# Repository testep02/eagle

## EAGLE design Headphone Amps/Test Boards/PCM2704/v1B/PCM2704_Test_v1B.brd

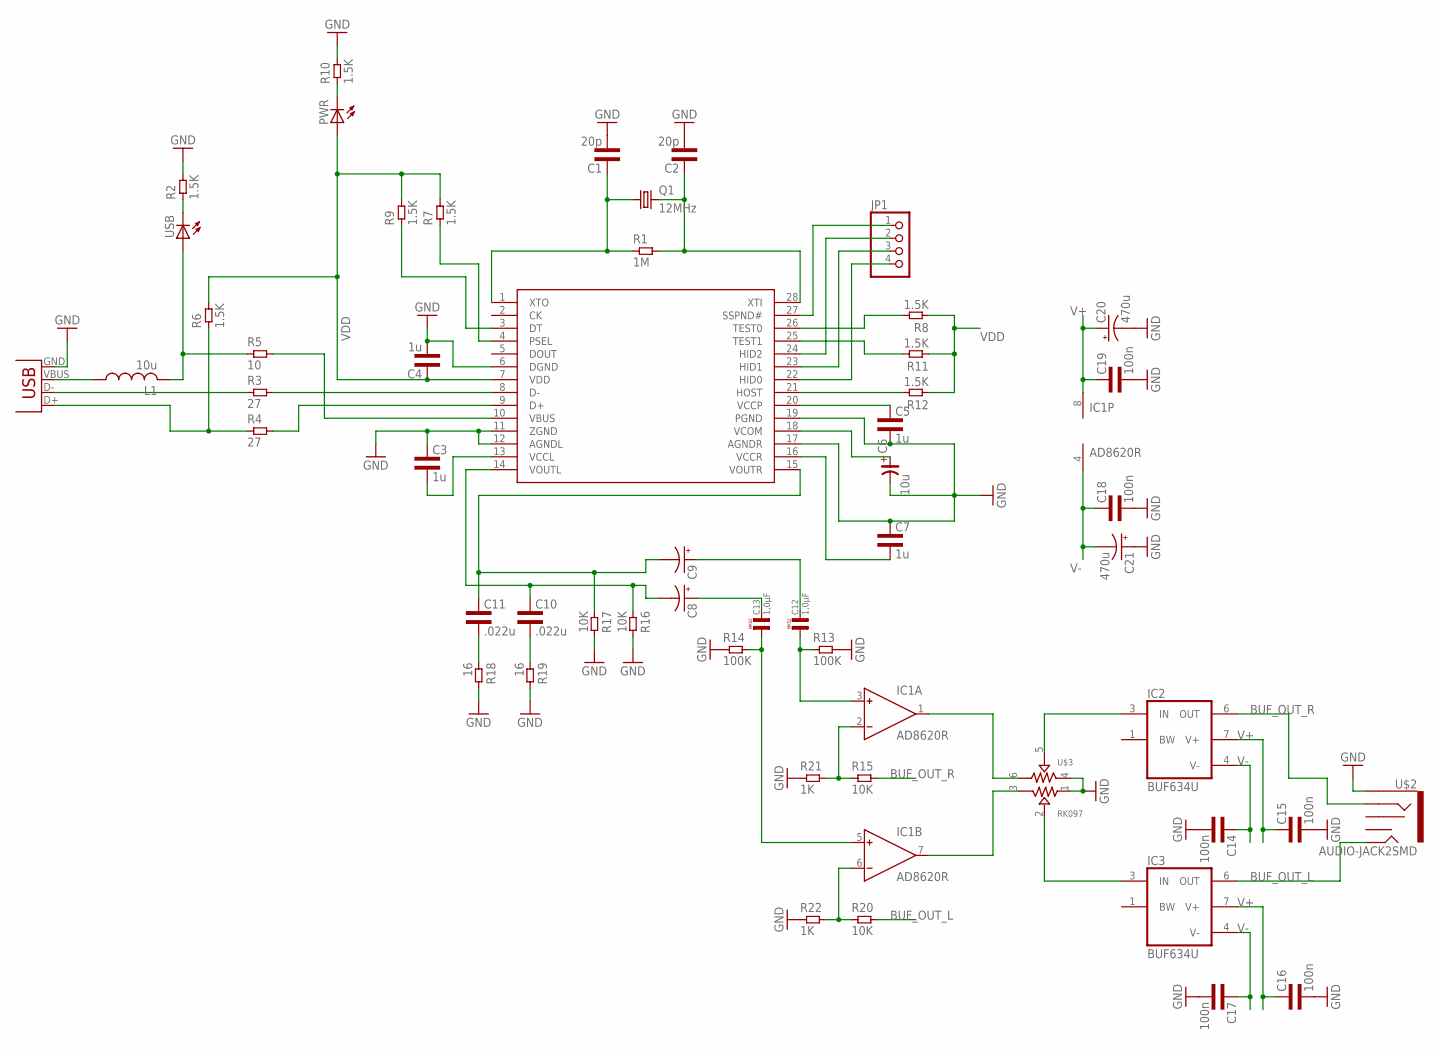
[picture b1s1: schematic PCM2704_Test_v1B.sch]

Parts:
C1, C2: 20p; 0603L3
C3, C4, C5, C7: 1u; 0603L3
C6: 10u; CE-010X030
C8, C9: CPOL-USE1.8-4; E1,8-4
C10, C11: .022u; 0603L3
C12, C13: 1,0µF; R5B5
C14, C15, C16, C17, C18, C19: 100n; 0603L3
C20, C21: 470u; E5-13
IC1: AD8620R; SO8
IC2, IC3: BUF634U; SO08
JP1: PINHD-1X4; 1X04
L1: 10u; L3225M
PWR: LEDCHIP-LED0603; CHIP-LED0603
Q1: 12MHz; HC49US
R1: 1M; 0603L3
R2, R6, R7, R8, R9, R10, R11, R12: 1.5K; 0603L3
R3, R4: 27; 0603L3
R5: 10; 0805L3
R13, R14: 100K; 0603L3
R15, R16, R17, R20: 10K; 0603L3
R18, R19: 16; 0603L3
R21, R22: 1K; 0603L3
U$1: PCM2704C
U$2: AUDIO-JACK2SMD; AUDIO-JACK-3.5MM-SMD
U$3: RK097
USB: LEDCHIP-LED0603; CHIP-LED0603
X1: USB-MB-S

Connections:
BUF_OUT_L: IC3.6 (OUT), R20.P$2 (2), U$2.TIP
BUF_OUT_R: IC2.6 (OUT), R15.P$2 (2), U$2.RING
GND: C1.P$2 (2), C2.P$2 (2), C3.P$1 (1), C4.P$2 (2), C5.P$2 (2), C6.-, C7.P$1 (1), C14.P$2 (2), C15.P$2 (2), C16.P$2 (2), C17.P$2 (2), C18.P$2 (2), C19.P$2 (2), C20.-, C21.+, R2.P$2 (2), R10.P$2 (2), R13.P$2 (2), R14.P$1 (1), R16.P$2 (2), R17.P$2 (2), R18.P$2 (2), R19.P$2 (2), R21.P$1 (1), R22.P$1 (1), U$1.6 (DGND), U$1.11 (ZGND), U$1.12 (AGNDL), U$1.17 (AGNDR), U$1.19 (PGND), U$2.SLEEVE, U$3.1, U$3.4, X1.GND
unnamed: C1.P$1 (1), Q1.1, R1.P$1 (1), U$1.1 (XTO)
unnamed: C2.P$1 (1), Q1.2, R1.P$2 (2), U$1.28 (XTI)
unnamed: R3.P$2 (2), U$1.8 (D-)
unnamed: C3.P$2 (2), U$1.13 (VCCL)
unnamed: R8.P$2 (2), U$1.26 (TEST0)
unnamed: R4.P$2 (2), U$1.9 (D+)
unnamed: L1.2, R5.1, USB.A
unnamed: R5.2, U$1.10 (VBUS)
unnamed: R11.P$2 (2), U$1.25 (TEST1)
unnamed: C9.-, C11.P$1 (1), R17.P$1 (1), U$1.15 (VOUTR)
unnamed: R12.P$2 (2), U$1.21 (HOST)
unnamed: JP1.1, U$1.27 (SSPND#)
unnamed: C5.P$1 (1), U$1.20 (VCCP)
unnamed: C6.+, U$1.18 (VCOM)
unnamed: C8.+, C13.2
unnamed: R9.P$1 (1), U$1.3 (DT)
unnamed: R2.P$1 (1), USB.C
unnamed: C9.+, C12.2
unnamed: JP1.2, U$1.24 (HID2)
unnamed: JP1.3, U$1.23 (HID1)
unnamed: JP1.4, U$1.22 (HID0)
unnamed: PWR.C, R10.P$1 (1)
unnamed: C7.P$2 (2), U$1.16 (VCCR)
unnamed: C8.-, C10.P$1 (1), R16.P$1 (1), U$1.14 (VOUTL)
unnamed: C12.1, IC1.3 (IN+), R13.P$1 (1)
unnamed: C13.1, IC1.5 (IN+), R14.P$2 (2)
unnamed: C11.P$2 (2), R18.P$1 (1)
unnamed: C10.P$2 (2), R19.P$1 (1)
unnamed: IC1.2 (IN-), R15.P$1 (1), R21.P$2 (2)
unnamed: IC1.6 (IN-), R20.P$1 (1), R22.P$2 (2)
unnamed: IC2.3 (IN), U$3.5
unnamed: IC3.3 (IN), U$3.2
unnamed: IC1.1 (OUT), U$3.6
unnamed: IC1.7 (OUT), U$3.3
PSEL: R7.P$1 (1), U$1.4 (PSEL)
USB_D_N: R3.P$1 (1), X1.D-
USB_D_P: R4.P$1 (1), R6.P$1 (1), X1.D+
V+: C15.P$1 (1), C16.P$1 (1), C19.P$1 (1), C20.+, IC1.8 (V+), IC2.7 (V+), IC3.7 (V+)
V-: C14.P$1 (1), C17.P$1 (1), C18.P$1 (1), C21.-, IC1.4 (V-), IC2.4 (V-), IC3.4 (V-)
VBUS_RAW: L1.1, X1.VBUS
VDD: C4.P$1 (1), PWR.A, R6.P$2 (2), R7.P$2 (2), R8.P$1 (1), R9.P$2 (2), R11.P$1 (1), R12.P$1 (1), U$1.7 (VDD)

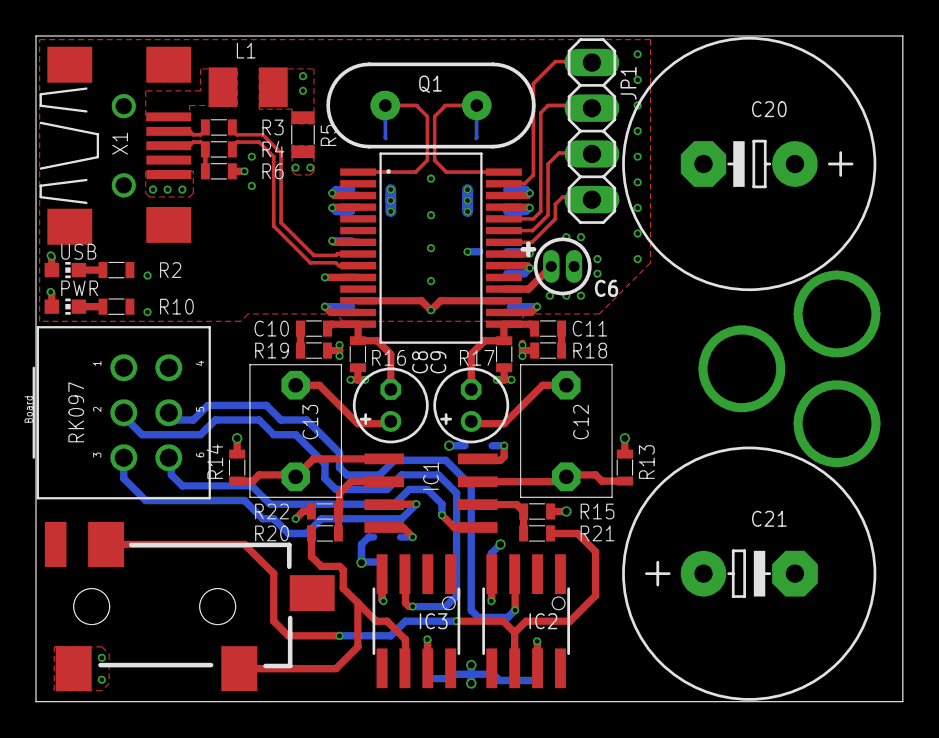
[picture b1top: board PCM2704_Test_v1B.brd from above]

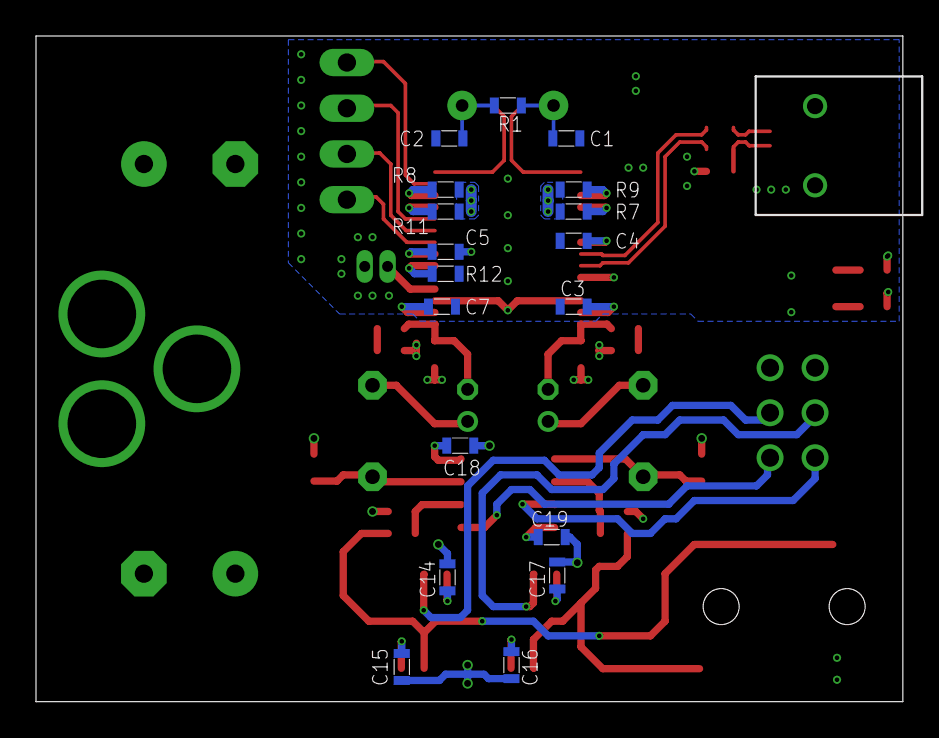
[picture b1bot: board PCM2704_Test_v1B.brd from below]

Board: 4 copper layers, 48.2 x 37.0 mm, 55 parts (18 on the bottom side), 44 nets.

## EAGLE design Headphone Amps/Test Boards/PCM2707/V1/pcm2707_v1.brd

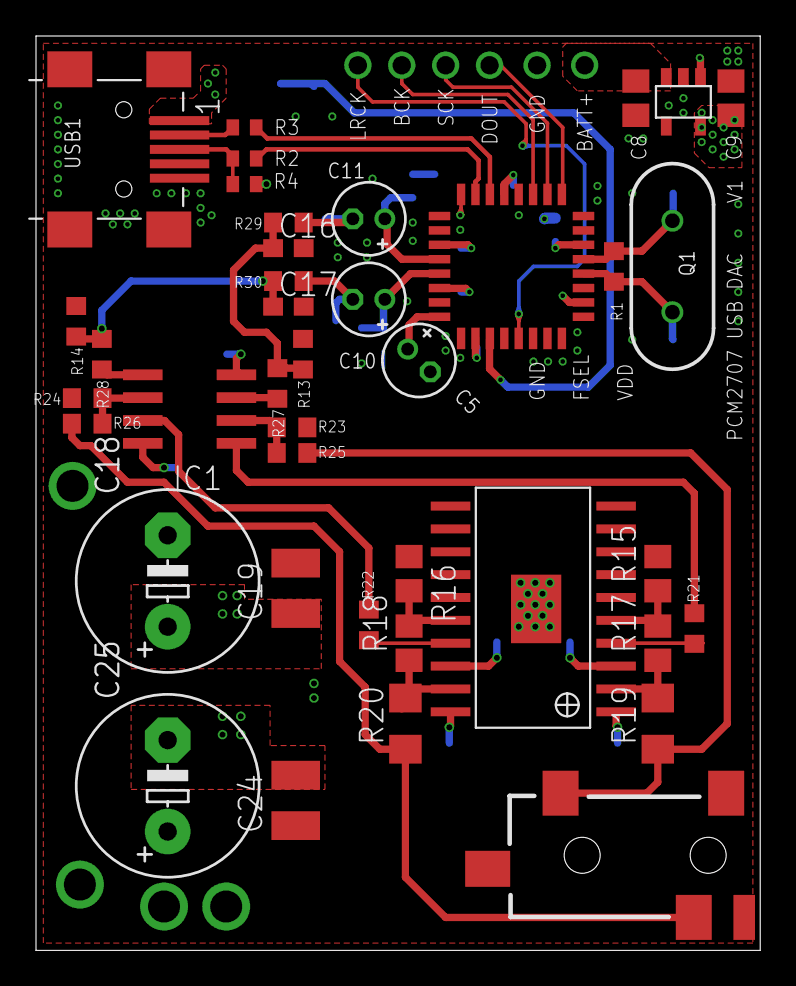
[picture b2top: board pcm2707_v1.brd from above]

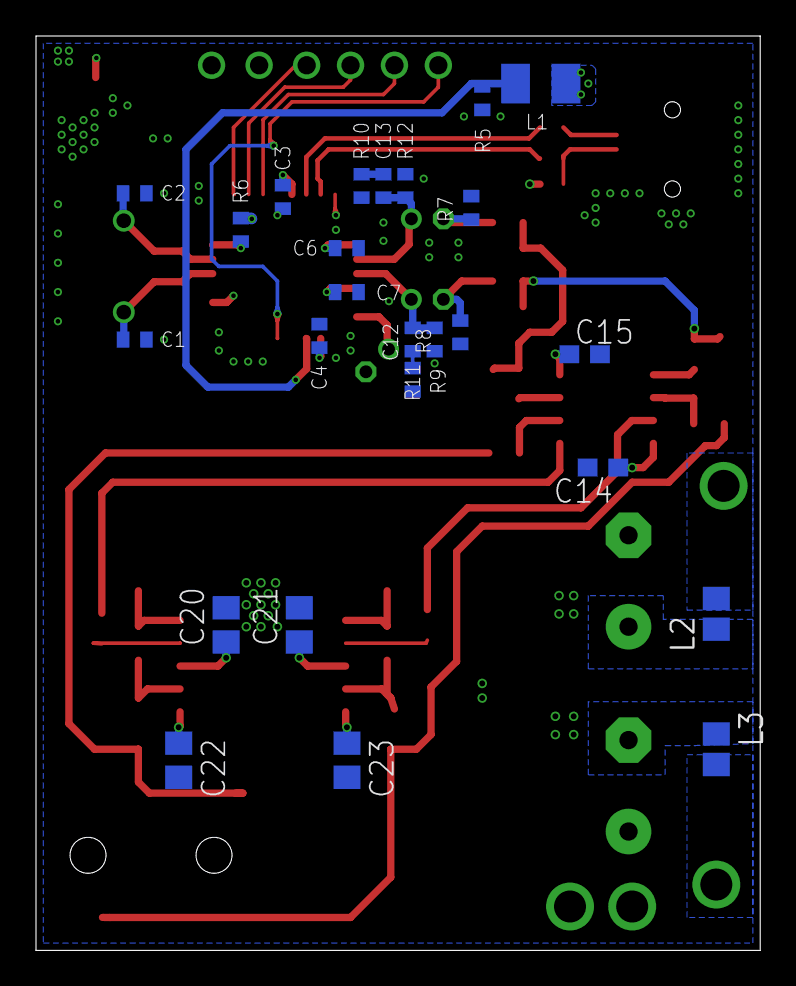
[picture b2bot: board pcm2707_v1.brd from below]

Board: 4 copper layers, 40.2 x 50.8 mm, 65 parts (25 on the bottom side), 37 nets.

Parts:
C1, C2: C0402
C3, C4, C6, C7, C12, C13: 100n; C0402
C5: E1,8-4
C8, C9: 1u; C0805
C10, C11: 100u; E1,8-4
C14: C0603
C15: 100n; C0603
C16, C17: 100p; C0603
C18, C25: 100u; E5-10,5
C19, C24: 10u; C1210
C20, C21, C22, C23: 100n; C0805
IC1: AD8620R; SO8
J2: AUDIO-JACK2SMD; AUDIO-JACK-3.5MM-SMD
L1: L3225M
L2, L3: FB805
LDO1: 3.3V; SOT-23
Q1: HC49US
R1: 1M; R0603
R2, R3, R4, R7, R8, R9, R10, R11, R12: 22; R0402
R5, R6: 1M; R0402
R13, R14: 22K; R0603
R15, R16, R17, R18: 1K; R0805
R19, R20: 10; R1206
R21, R22, R27, R28: 100; R0603
R23, R24, R29, R30: 1K; R0603
R25, R26: 2K; R0603
U$1: PCM2707
U$2: TPA6120_TPA6120
USB1: CON-USB-F-MINI-B; CONN_USB_MINI-B

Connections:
AMP_OUT_L: J2.TIP, R19.1, R25.2
AMP_OUT_R: J2.RING, R20.1, R26.1
D+: R2.1, U$1.23
D-: R3.1, U$1.22
DAC_OUT_L: C11.-, R7.2, R29.1
DAC_OUT_R: C10.-, R8.2, R30.1
GND: C1.1, C2.1, C3.2, C4.2, C5.-, C6.2, C7.2, C8.2, C9.2, C16.2, C17.2, C18.-, C19.2, C20.2, C21.2, C22.2, C23.2, C24.1, C25.+, J2.SLEEVE, LDO1.2, R5.2, R7.1, R8.1, R9.1, R10.1, R11.1, R12.1, R13.1, R14.1, R15.2, R16.1, R23.2, R24.2, U$1.1, U$1.16, U$1.20, U$1.25, U$1.26, U$1.31, U$2.6, U$2.7, U$2.8, U$2.9, U$2.10, U$2.11, U$2.12, U$2.13, U$2.14, U$2.15, U$2.21
unnamed: C5.+, U$1.32
unnamed: C10.+, C12.1, R11.2, U$1.29
unnamed: C11.+, C13.1, R12.2, U$1.28
unnamed: IC1.5, R28.2
unnamed: IC1.3, R27.2
unnamed: C12.2, R9.2
unnamed: C13.2, R10.2
unnamed: R6.1, U$1.14
unnamed: IC1.1, R21.2
unnamed: C16.1, R13.2, R27.1, R29.2
unnamed: IC1.7, R22.2
unnamed: C17.1, R14.2, R28.1, R30.2
unnamed: IC1.2, R23.1, R25.1
unnamed: IC1.6, R24.1, R26.2
unnamed: R17.1, R19.2, U$2.2
unnamed: R18.1, R20.2, U$2.19
unnamed: R15.1, R17.2, U$2.5
unnamed: R16.2, R18.2, U$2.16
unnamed: R21.1, U$2.4
unnamed: R22.1, U$2.17
USB_DN: R3.2, USB1.D-
USB_DP: R2.2, R4.1, USB1.D+
USB_VBUS: L1.1, USB1.VUSB
V+: C14.1, C18.+, C19.1, C20.1, C21.1, IC1.8, L2.1, U$2.3, U$2.18
V-: C15.1, C22.1, C23.1, C24.2, C25.-, IC1.4, L3.1, U$2.1, U$2.20
VBUS: L1.2, R5.1, U$1.3
VDD: C3.1, C4.1, C6.1, C7.1, C9.1, LDO1.5, R4.2, R6.2, U$1.2, U$1.10, U$1.21, U$1.24, U$1.27, U$1.30
VIN: C8.1, LDO1.1, LDO1.3
XTI: C1.2, Q1.1, R1.1, U$1.12
XTO: C2.2, Q1.2, R1.2, U$1.13

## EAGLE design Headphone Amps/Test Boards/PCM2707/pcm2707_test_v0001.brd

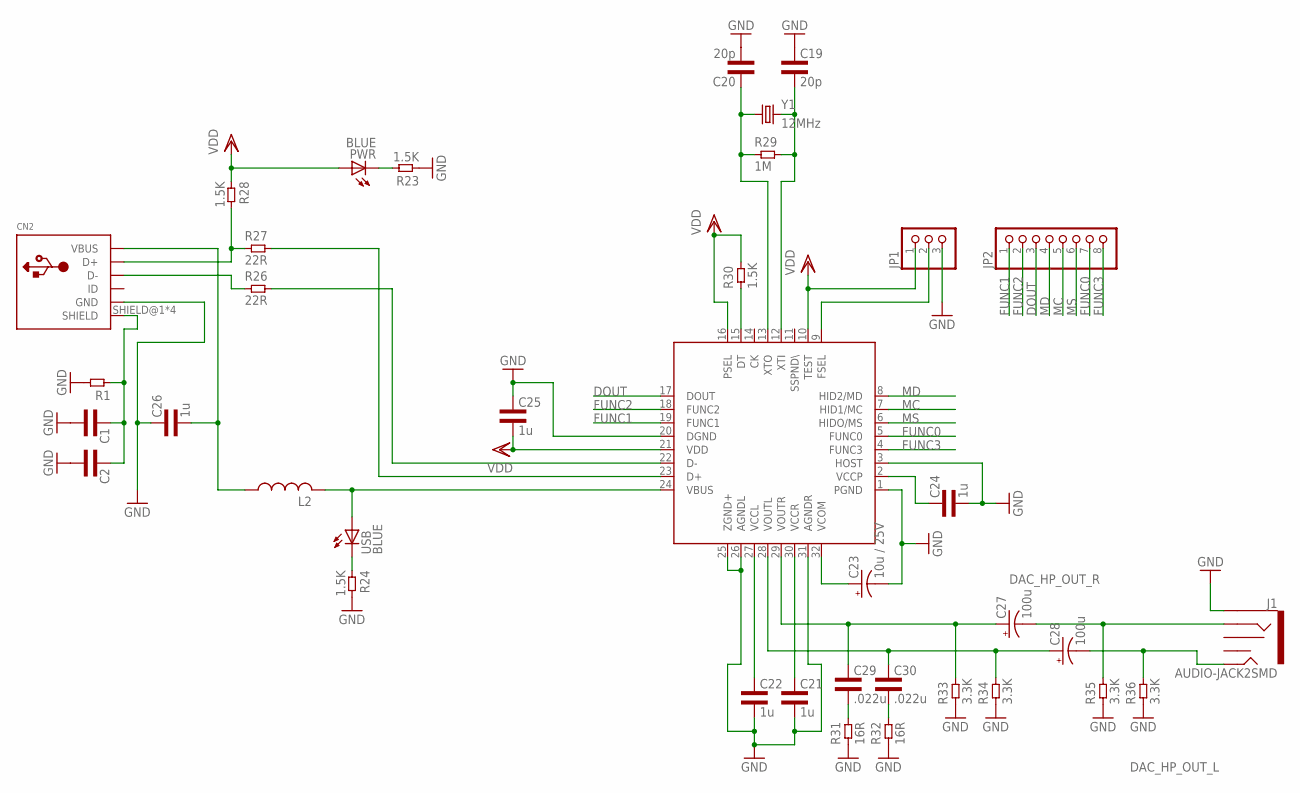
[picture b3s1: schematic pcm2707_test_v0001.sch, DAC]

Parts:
C1, C2: CAP0603L3; 0603L3
C19, C20: 20p; 0603L3
C21, C22, C24, C25, C26: 1u; 0603L3
C23: 10u / 25V; E1,8-4
C27, C28: 100u; E2-5
C29, C30: .022u; 0603L3
CN2: USBMINIB; USB-MINIB
J1: AUDIO-JACK2SMD; AUDIO-JACK-3.5MM-SMD
JP1: PINHD-1X3; 1X03
JP2: PINHD-1X8; 1X08
L2: RCL_L-USL3225M; RCL_L3225M
PWR: BLUE; LED-0603
R1: RES0603L3; 0603L3
R23, R24, R28, R30: 1.5K; 0603L3
R26, R27: 22R; 0603L3
R29: 1M; 0603L3
R31, R32: 16R; 0603L3
R33, R34, R35, R36: 3.3K; 0603L3
U$1: PCM2707_V1_PCM2704C_PCM2707
USB: BLUE; LED-0603
Y1: 12MHz; HC49US

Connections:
DAC_HP_OUT_L: C28.-, J1.TIP, R36.P$2 (2)
DAC_HP_OUT_R: C27.-, J1.RING, R35.P$2 (2)
DOUT: JP2.3, U$1.17 (DOUT)
FUNC0: JP2.7, U$1.5 (FUNC0)
FUNC1: JP2.1, U$1.19 (FUNC1)
FUNC2: JP2.2, U$1.18 (FUNC2)
FUNC3: JP2.8, U$1.4 (FUNC3)
GND: C1.P$2 (2), C2.P$2 (2), C19.P$1 (1), C20.P$2 (2), C21.P$2 (2), C22.P$2 (2), C23.-, C24.P$2 (2), C25.P$1 (1), C26.P$1 (1), CN2.GND, J1.SLEEVE, JP1.3, R1.P$2 (2), R23.P$1 (1), R24.P$2 (2), R31.P$1 (1), R32.P$1 (1), R33.P$1 (1), R34.P$1 (1), R35.P$1 (1), R36.P$1 (1), U$1.1 (PGND), U$1.3 (HOST), U$1.20 (DGND), U$1.25 (ZGND+), U$1.26 (AGNDL), U$1.31 (AGNDR)
MC: JP2.5, U$1.7 (HID1/MC)
MD: JP2.4, U$1.8 (HID2/MD)
MS: JP2.6, U$1.6 (HIDO/MS)
unnamed: JP1.2, U$1.9 (FSEL)
unnamed: PWR.C, R23.P$2 (2)
unnamed: C1.P$1 (1), C2.P$1 (1), CN2.SHIELD@1 (SHIELD), CN2.SHIELD@2 (SHIELD), CN2.SHIELD@3 (SHIELD), CN2.SHIELD@4 (SHIELD), R1.P$1 (1)
unnamed: R24.P$1 (1), USB.C
unnamed: CN2.D+, R27.P$1 (1), R28.P$2 (2)
unnamed: CN2.D-, R26.P$1 (1)
unnamed: R27.P$2 (2), U$1.23 (D+)
unnamed: R26.P$2 (2), U$1.22 (D-)
unnamed: C20.P$1 (1), R29.P$1 (1), U$1.13 (XTO), Y1.1
unnamed: C19.P$2 (2), R29.P$2 (2), U$1.12 (XTI), Y1.2
unnamed: C22.P$1 (1), U$1.27 (VCCL)
unnamed: C21.P$1 (1), U$1.30 (VCCR)
unnamed: C23.+, U$1.32 (VCOM)
unnamed: C29.P$2 (2), R31.P$2 (2)
unnamed: C24.P$1 (1), U$1.2 (VCCP)
unnamed: C27.+, C29.P$1 (1), R33.P$2 (2), U$1.29 (VOUTR)
unnamed: C28.+, C30.P$1 (1), R34.P$2 (2), U$1.28 (VOUTL)
unnamed: R30.P$1 (1), U$1.15 (DT)
unnamed: C30.P$2 (2), R32.P$2 (2)
VBUS: L2.2, U$1.24 (VBUS), USB.A
VBUS_RAW: C26.P$2 (2), CN2.VBUS, L2.1
VDD: C25.P$2 (2), JP1.1, PWR.A, R28.P$1 (1), R30.P$2 (2), U$1.10 (TEST), U$1.16 (PSEL), U$1.21 (VDD)

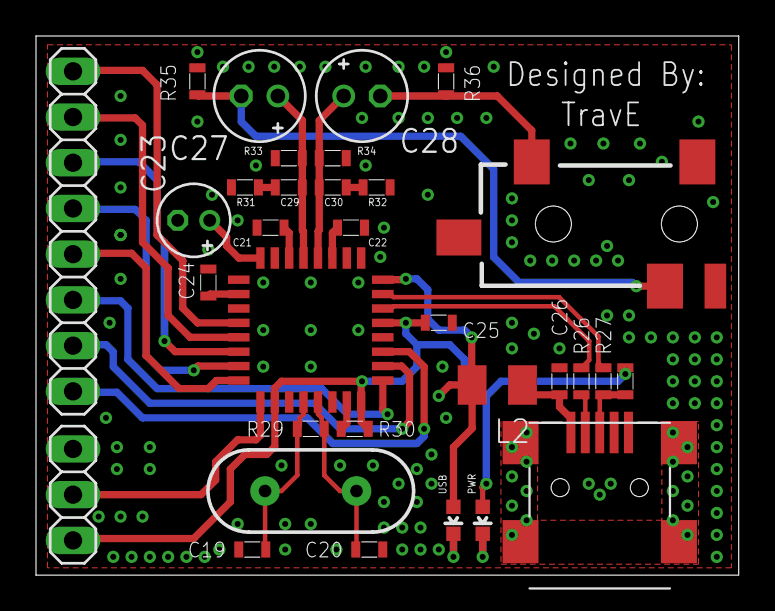
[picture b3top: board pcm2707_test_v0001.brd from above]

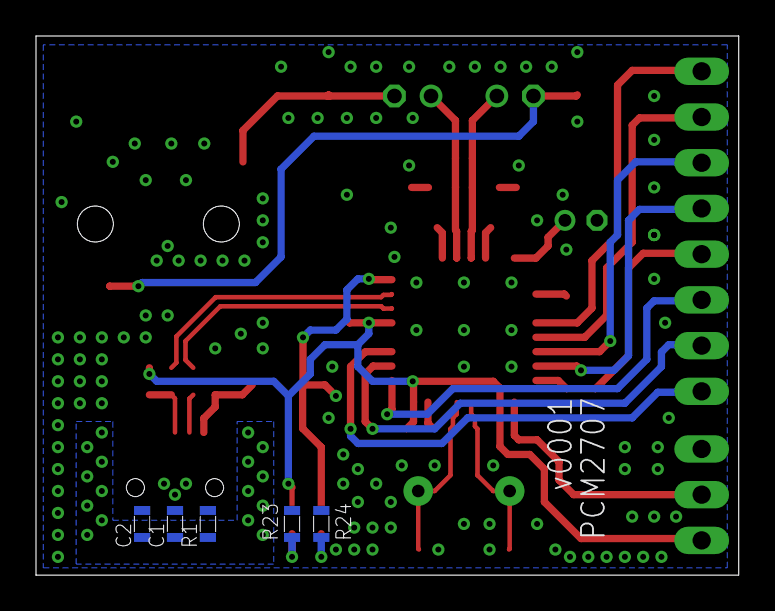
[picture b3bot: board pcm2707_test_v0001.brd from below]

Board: 2 copper layers, 39.0 x 30.0 mm, 37 parts (5 on the bottom side), 33 nets.

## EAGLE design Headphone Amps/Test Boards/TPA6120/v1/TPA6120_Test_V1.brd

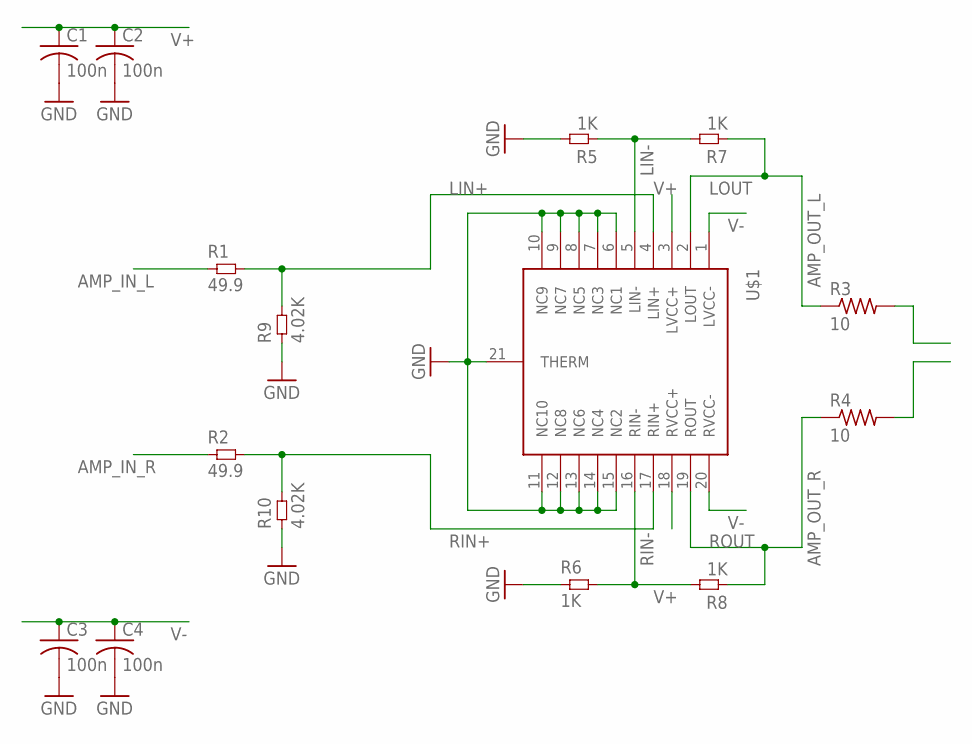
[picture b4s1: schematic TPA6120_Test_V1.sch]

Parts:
C1, C2, C3, C4: 100n; C0603
R1, R2: 49.9; 0603L3
R3, R4: 10; R1206
R5, R6, R7, R8: 1K; 0603L3
R9, R10: 4.02K; 0603L3
U$1: TPA6120_TPA6120

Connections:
AMP_IN_L: R1.P$1 (1)
AMP_IN_R: R2.P$1 (1)
AMP_OUT_L: R3.2
AMP_OUT_R: R4.2
GND: C1.2, C2.2, C3.2, C4.2, R5.P$2 (2), R6.P$1 (1), R9.P$1 (1), R10.P$1 (1), U$1.6 (NC1), U$1.7 (NC3), U$1.8 (NC5), U$1.9 (NC7), U$1.10 (NC9), U$1.11 (NC10), U$1.12 (NC8), U$1.13 (NC6), U$1.14 (NC4), U$1.15 (NC2), U$1.21 (THERM)
LIN+: R1.P$2 (2), R9.P$2 (2), U$1.4 (LIN+)
LIN-: R5.P$1 (1), R7.P$2 (2), U$1.5 (LIN-)
LOUT: R3.1, R7.P$1 (1), U$1.2 (LOUT)
RIN+: R2.P$2 (2), R10.P$2 (2), U$1.17 (RIN+)
RIN-: R6.P$2 (2), R8.P$2 (2), U$1.16 (RIN-)
ROUT: R4.1, R8.P$1 (1), U$1.19 (ROUT)
V+: C1.1, C2.1, U$1.3 (LVCC+), U$1.18 (RVCC+)
V-: C3.1, C4.1, U$1.1 (LVCC-), U$1.20 (RVCC-)

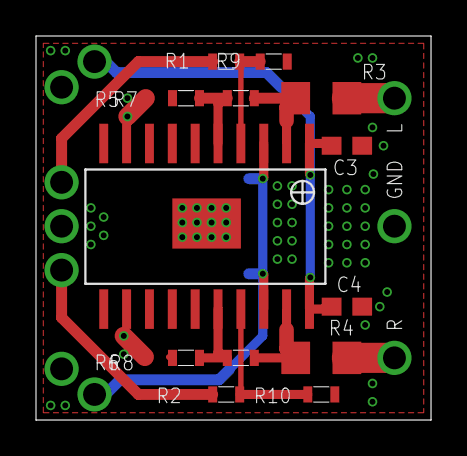
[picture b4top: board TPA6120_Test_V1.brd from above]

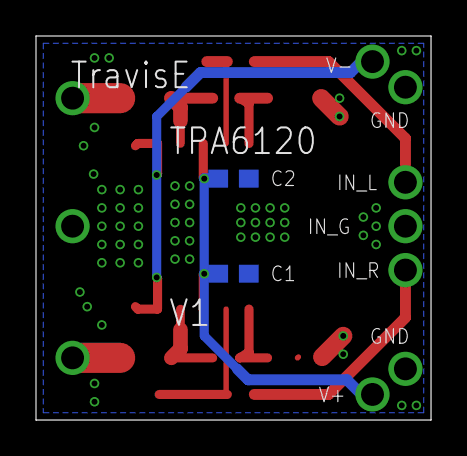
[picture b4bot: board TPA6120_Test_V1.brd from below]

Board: 2 copper layers, 21.9 x 21.3 mm, 15 parts (2 on the bottom side), 9 nets.

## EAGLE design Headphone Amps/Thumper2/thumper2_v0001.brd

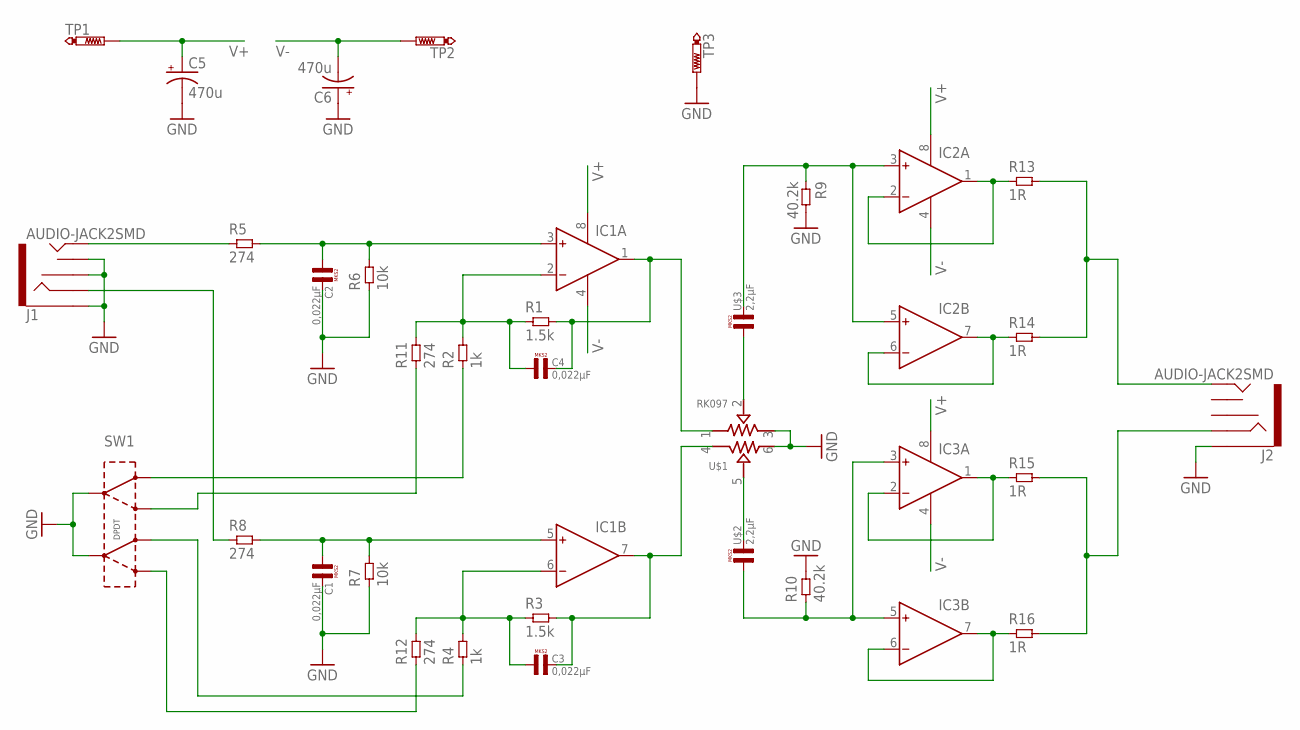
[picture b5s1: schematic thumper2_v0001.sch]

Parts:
C1, C2, C3, C4: 0,022µF; R5B2K5
C5, C6: 470u; 153CLV-1010
IC1, IC2, IC3: AD8620R; SO8
J1, J2: AUDIO-JACK2SMD; AUDIO-JACK-3.5MM-SMD
R1, R3: 1.5k; 0603L3
R2, R4: 1k; 0603L3
R5, R8, R11, R12: 274; 0603L3
R6, R7: 10k; 0603L3
R9, R10: 40.2k; 0603L3
R13, R14, R15, R16: 1R; 1206L3
SW1: DPDTDPDT-2X2.5; DPDT-2X2.5
TP1, TP2, TP3: PTR1PAD1-20; P1-20
U$1: RK097
U$2, U$3: 2,2µF; R5B7K2

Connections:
GND: C1.2, C2.2, C5.-, C6.+, J1.RSH, J1.SLEEVE, J1.TSH, J2.SLEEVE, R6.P$1 (1), R7.P$1 (1), R9.P$2 (2), R10.P$2 (2), SW1.2 (INA), SW1.5 (INB), TP3.TP, U$1.3, U$1.6
unnamed: C2.1, IC1.3 (IN+), R5.P$2 (2), R6.P$2 (2)
unnamed: C4.1, IC1.2 (IN-), R1.P$1 (1), R2.P$2 (2), R11.P$2 (2)
unnamed: C4.2, IC1.1 (OUT), R1.P$2 (2), U$1.1
unnamed: C1.1, IC1.5 (IN+), R7.P$2 (2), R8.P$2 (2)
unnamed: C3.2, IC1.7 (OUT), R3.P$2 (2), U$1.4
unnamed: C3.1, IC1.6 (IN-), R3.P$1 (1), R4.P$2 (2), R12.P$2 (2)
unnamed: J2.TIP, R13.2, R14.2
unnamed: U$1.5, U$2.2
unnamed: U$1.2, U$3.1
unnamed: J2.RING, R15.2, R16.2
unnamed: IC3.3 (IN+), IC3.5 (IN+), R10.P$1 (1), U$2.1
unnamed: IC2.3 (IN+), IC2.5 (IN+), R9.P$1 (1), U$3.2
unnamed: IC2.6 (IN-), IC2.7 (OUT), R14.1
unnamed: IC3.1 (OUT), IC3.2 (IN-), R15.1
unnamed: IC3.6 (IN-), IC3.7 (OUT), R16.1
unnamed: IC2.1 (OUT), IC2.2 (IN-), R13.1
unnamed: R12.P$1 (1), SW1.6 (OUTB2)
unnamed: R11.P$1 (1), SW1.3 (OUTA2)
unnamed: R2.P$1 (1), SW1.1 (OUTA1)
unnamed: R4.P$1 (1), SW1.4 (OUTB1)
unnamed: J1.RING, R8.P$1 (1)
unnamed: J1.TIP, R5.P$1 (1)
V+: C5.+, IC1.8 (V+), IC2.8 (V+), IC3.8 (V+), TP1.TP
V-: C6.-, IC1.4 (V-), IC2.4 (V-), IC3.4 (V-), TP2.TP

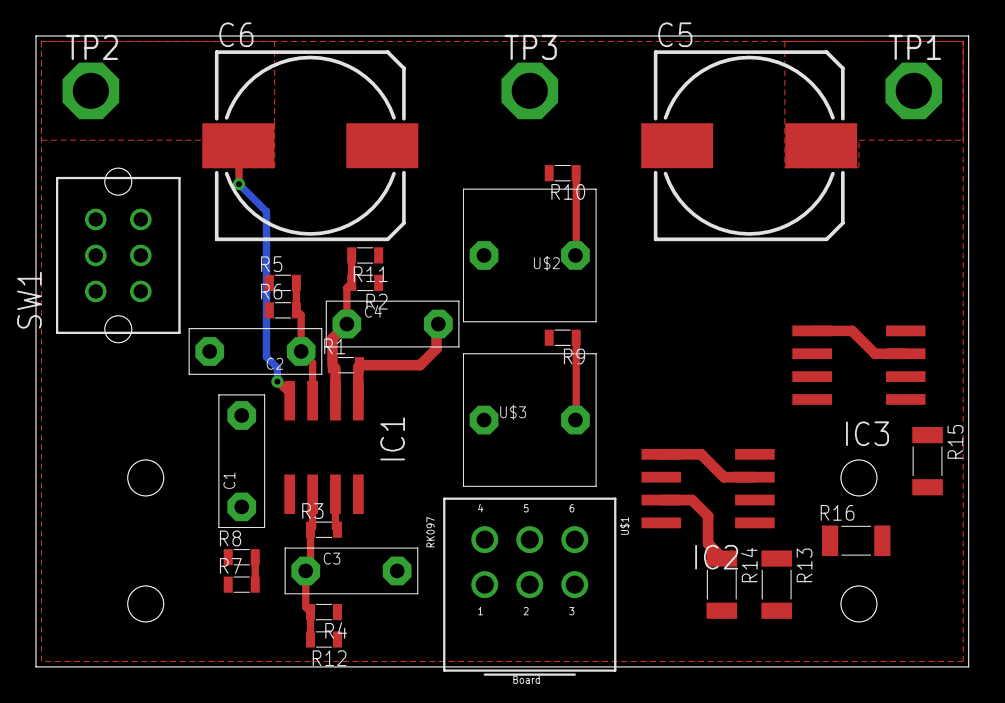
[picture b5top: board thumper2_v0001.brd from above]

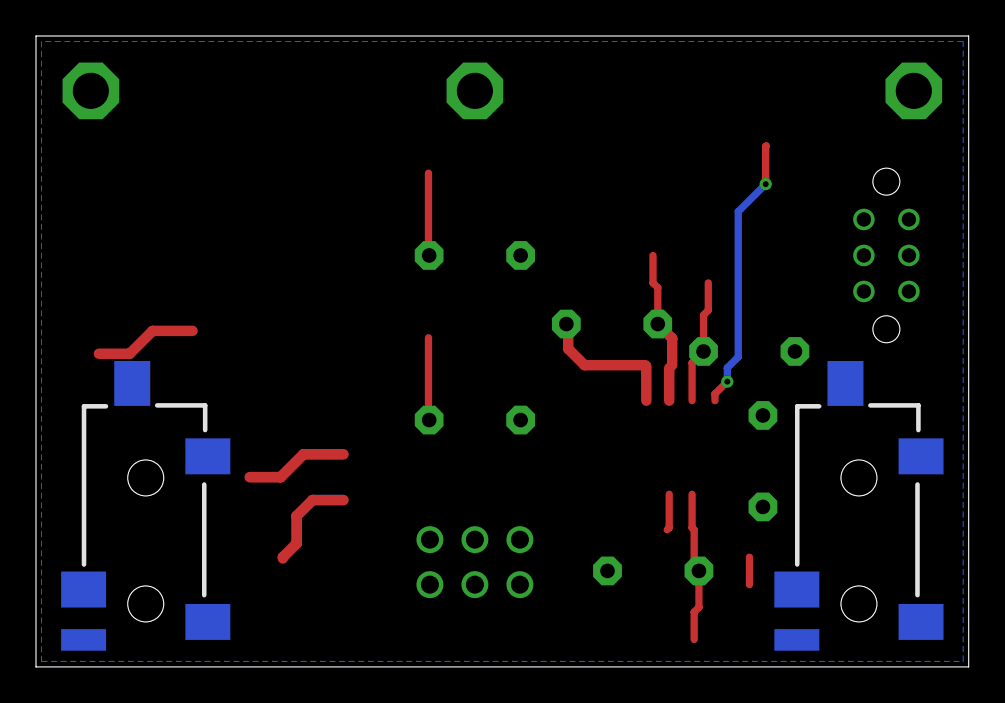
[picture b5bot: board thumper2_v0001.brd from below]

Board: 2 copper layers, 51.8 x 35.1 mm, 34 parts (2 on the bottom side), 25 nets.

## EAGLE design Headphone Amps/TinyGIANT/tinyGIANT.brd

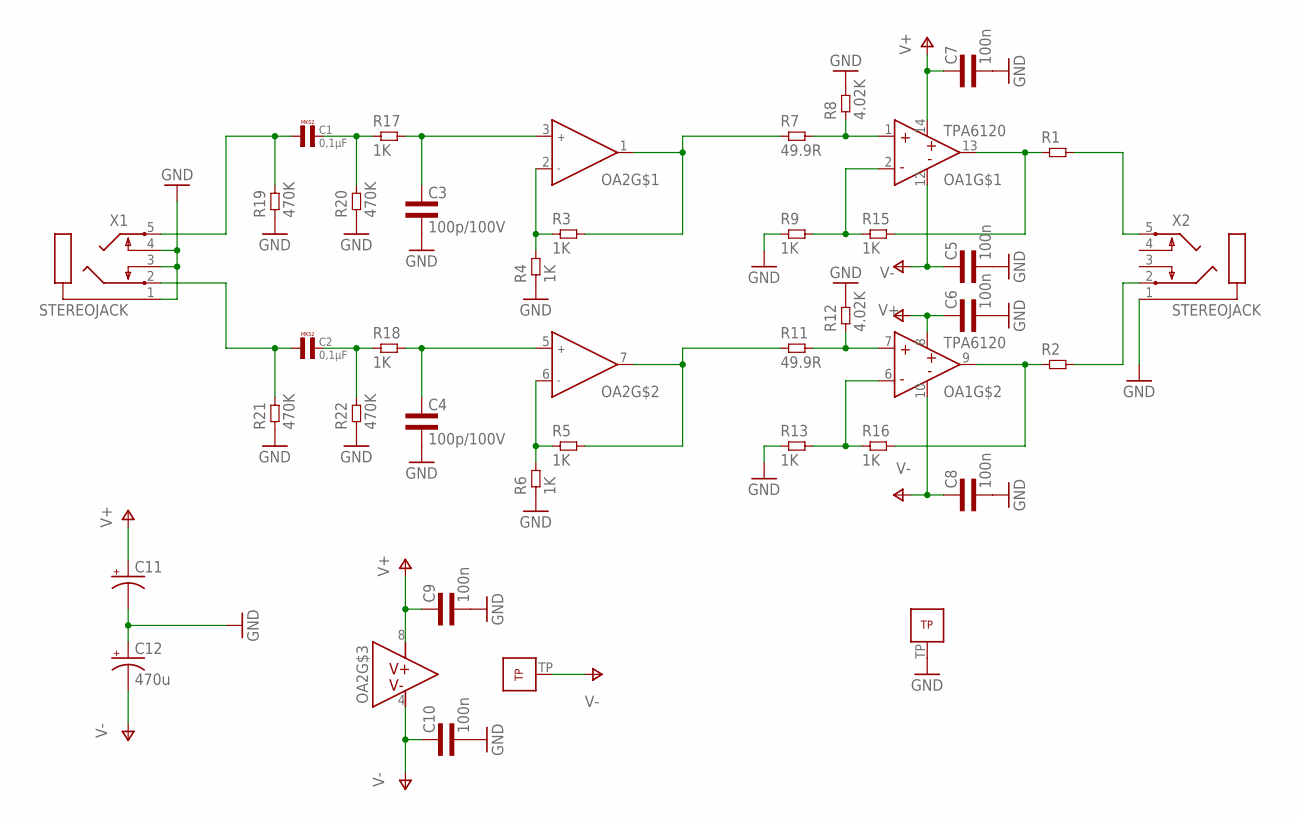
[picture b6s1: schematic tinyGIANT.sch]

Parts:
C1, C2: 0,1µF; R5B2K5
C3, C4: 100p/100V; 0805L3
C5, C6, C7, C8, C9, C10: 100n; 0603L3
C11: CPOL-USCT7343; CT7343
C12: 470u; CT7343
OA1: TPA6120QFN; S-PVQFN-N14
OA2: OPA1612; S-PWSON-N8
R1, R2: RES1206L3; 1206L3
R3, R4, R5, R6, R9, R13, R15, R16: 1K; 0603L3
R7, R11: 49.9R; 0805L3
R8, R12: 4.02K; 0805L3
R17, R18: 1K; 0805L3
R19, R20, R21, R22: 470K; 0805L3
X1, X2: STEREOJACK; STX3100

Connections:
BUF_INV_L: OA1.2 (IN-), R9.P$2 (2), R15.P$1 (1)
BUF_INV_R: OA1.6 (IN-), R13.P$2 (2), R16.P$1 (1)
BUF_IN_L: OA1.1 (IN+), R7.2, R8.1
BUF_IN_R: OA1.7 (IN+), R11.2, R12.1
BUF_OUT_L: OA1.13 (OUT), R1.1, R15.P$2 (2)
BUF_OUT_R: OA1.9 (OUT), R2.1, R16.P$2 (2)
CAP_OUT_L: C1.2, R17.1, R20.2
CAP_OUT_R: C2.2, R18.1, R22.2
GND: C3.2, C4.2, C5.P$2 (2), C6.P$2 (2), C7.P$2 (2), C8.P$2 (2), C9.P$2 (2), C10.P$2 (2), C11.-, C12.+, OA1.TP, R4.P$1 (1), R6.P$1 (1), R8.2, R9.P$1 (1), R12.2, R13.P$1 (1), R19.1, R20.1, R21.1, R22.1, X1.1, X1.3, X1.4, X2.1
HP_IN_L: C1.1, R19.2, X1.5
HP_IN_R: C2.1, R21.2, X1.2
HP_OUT_L: R1.2, X2.5
HP_OUT_R: R2.2, X2.2
OA_INV_L: OA2.2 (INA-), R3.P$1 (1), R4.P$2 (2)
OA_INV_R: OA2.6 (INB-), R5.P$1 (1), R6.P$2 (2)
OA_IN_L: C3.1, OA2.3 (INA+), R17.2
OA_IN_R: C4.1, OA2.5 (INB+), R18.2
OA_OUT_L: OA2.1 (OUTA), R3.P$2 (2), R7.1
OA_OUT_R: OA2.7 (OUTB), R5.P$2 (2), R11.1
V+: C6.P$1 (1), C7.P$1 (1), C9.P$1 (1), C11.+, OA1.8 (V+), OA1.14 (V+), OA2.8 (V+)
V-: C5.P$1 (1), C8.P$1 (1), C10.P$1 (1), C12.-, OA1.10 (V-), OA1.12 (V-), OA2.4 (V-), OA2.TP

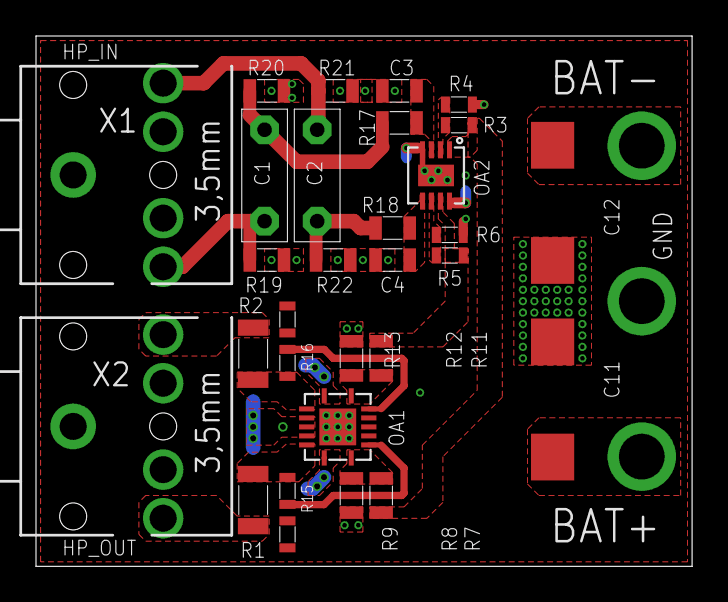
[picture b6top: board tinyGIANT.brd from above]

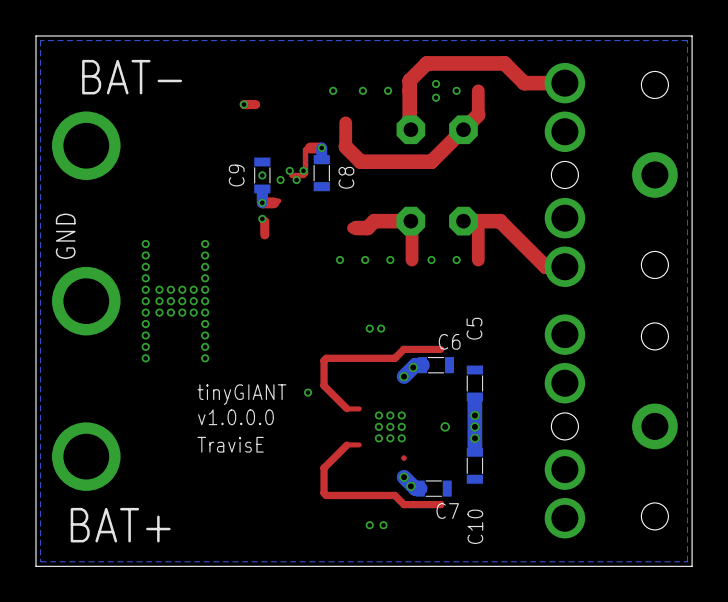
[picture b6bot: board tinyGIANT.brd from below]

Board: 4 copper layers, 36.4 x 29.5 mm, 36 parts (6 on the bottom side), 21 nets.

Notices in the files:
parts and their libraries:
SparkFun-FreqCtrl: Licensing: CC v3.0 Share-Alike You are welcome to use this library for commercial purposes.
rc-master: Copyright (C) 2007, Bob Starr
SparkFun-FreqCtrl: Licensing: CC
